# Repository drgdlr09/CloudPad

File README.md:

# CloudPad
A simple nine-key macropad that can open up my favorite and most-used apps

**Bill of Materials**
- Seeed XIAO RP2040
- 9 through-hole 1N4148 diodes
- 9 MX-style switches
- 9 white blank DSA keycaps
- 1 EC11 rotary encoder

I opted to use a simplified sandwich mount for ease of design and assembly. I may iterate on this in the future to make it more visually pleasing.

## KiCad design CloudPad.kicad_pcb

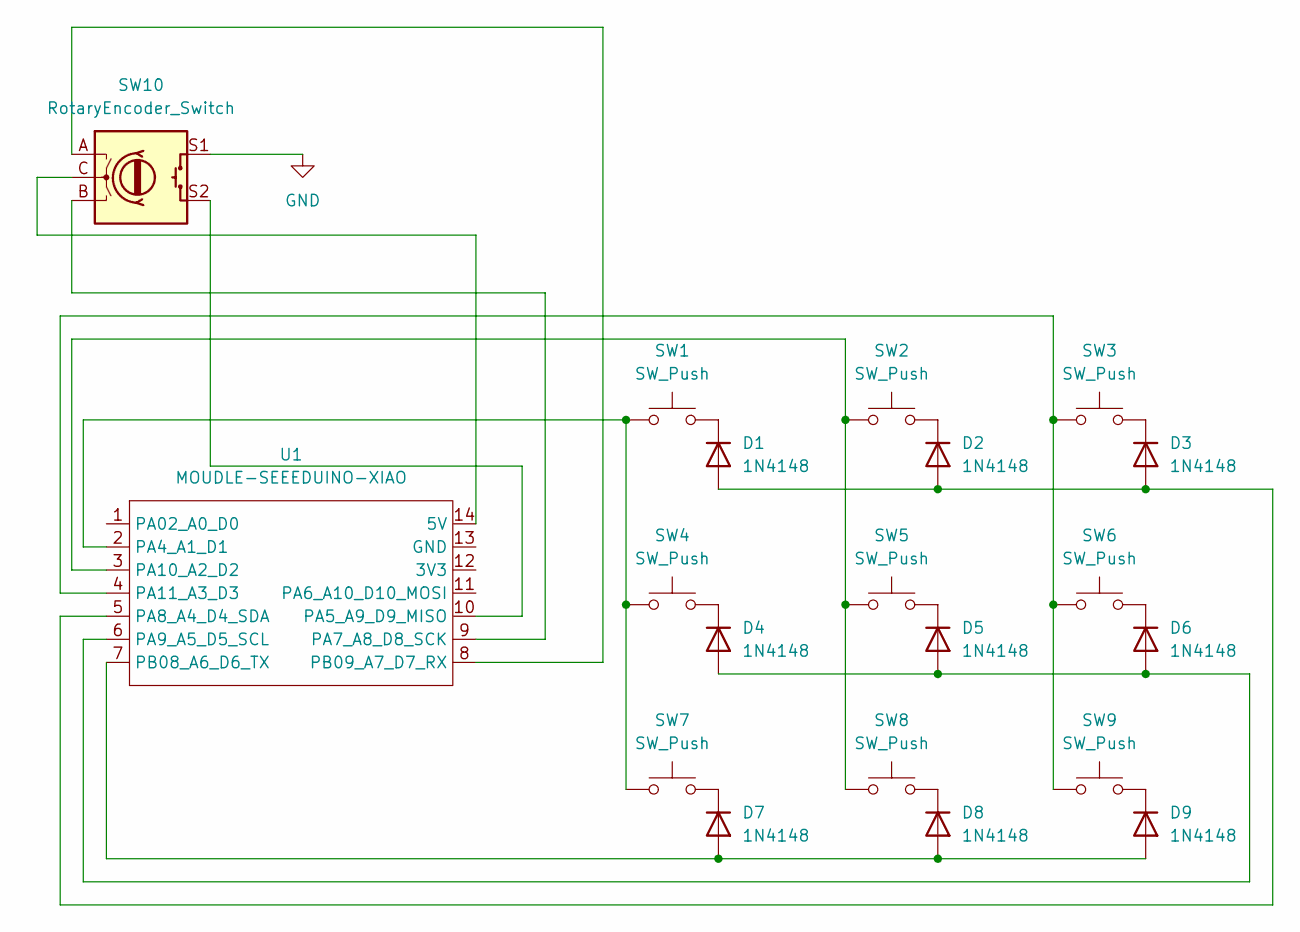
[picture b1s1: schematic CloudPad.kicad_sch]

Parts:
D1, D2, D3, D4, D5, D6, D7, D8, D9: 1N4148; D_DO-35_SOD27_P7.62mm_Horizontal
SW1, SW2, SW3, SW4, SW5, SW6, SW7, SW8, SW9: SW_Push; SW_Cherry_MX_1.00u_PCB
SW10: RotaryEncoder_Switch; RotaryEncoder_Alps_EC11E-Switch_Vertical_H20mm
U1: MOUDLE-SEEEDUINO-XIAO; XIAO-Generic-Hybrid-14P-2.54-21X17.8MM

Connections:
GND: SW10.S1
unnamed: D1.2 (A), D2.2 (A), D3.2 (A), U1.5 (PA8_A4_D4_SDA)
unnamed: D1.1 (K), SW1.2
unnamed: D2.1 (K), SW2.2
unnamed: D3.1 (K), SW3.2
unnamed: D4.2 (A), D5.2 (A), D6.2 (A), U1.6 (PA9_A5_D5_SCL)
unnamed: D4.1 (K), SW4.2
unnamed: D5.1 (K), SW5.2
unnamed: D6.1 (K), SW6.2
unnamed: D7.2 (A), D8.2 (A), D9.2 (A), U1.7 (PB08_A6_D6_TX)
unnamed: D7.1 (K), SW7.2
unnamed: D8.1 (K), SW8.2
unnamed: D9.1 (K), SW9.2
unnamed: SW10.C, U1.14 (5V)
unnamed: SW1.1, SW4.1, SW7.1, U1.2 (PA4_A1_D1)
unnamed: SW10.S2, U1.10 (PA5_A9_D9_MISO)
unnamed: SW10.B, U1.9 (PA7_A8_D8_SCK)
unnamed: SW2.1, SW5.1, SW8.1, U1.3 (PA10_A2_D2)
unnamed: SW3.1, SW6.1, SW9.1, U1.4 (PA11_A3_D3)
unnamed: SW10.A, U1.8 (PB09_A7_D7_RX)

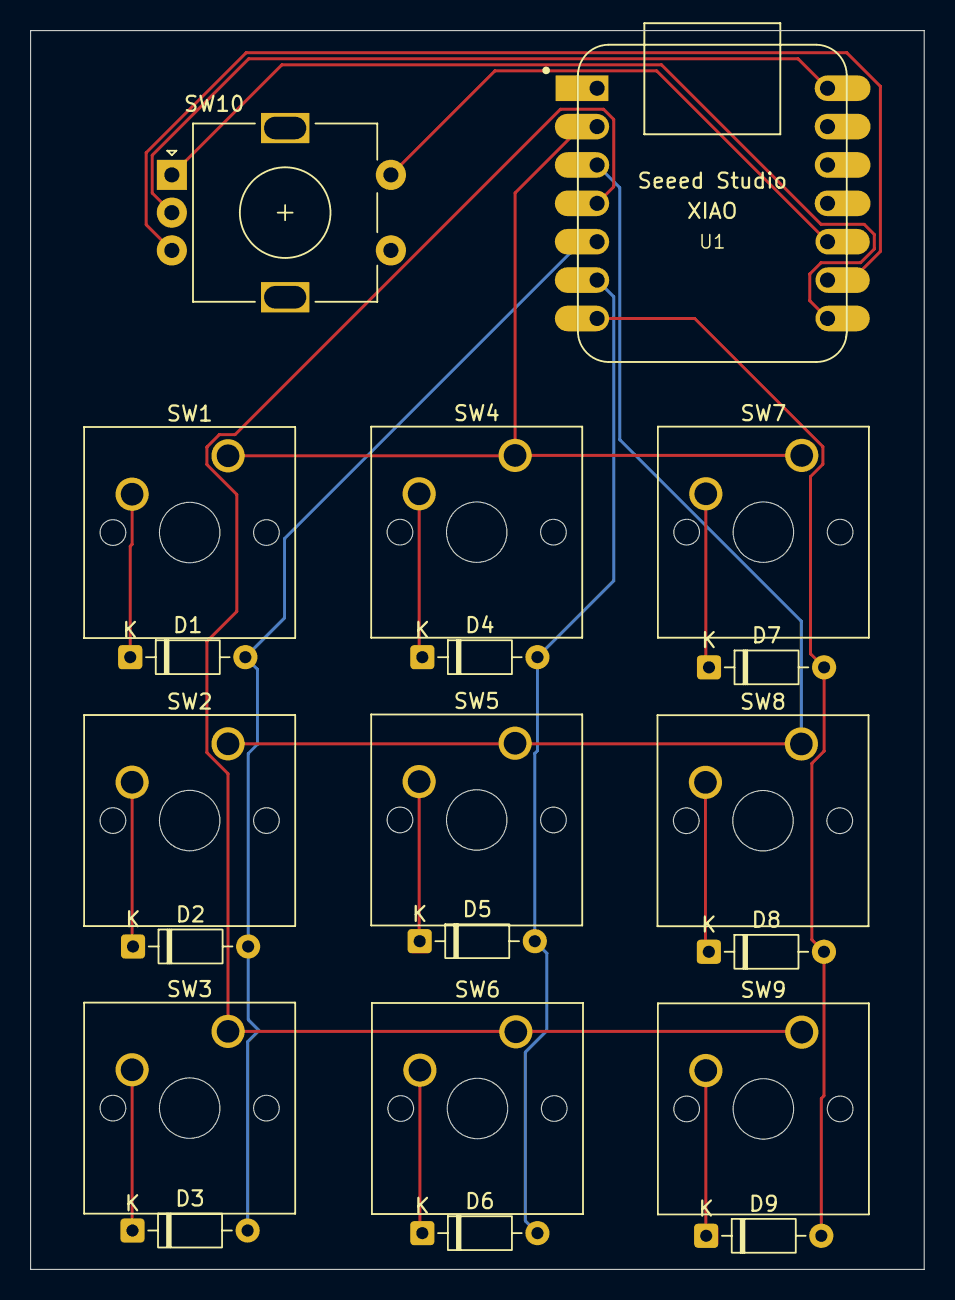
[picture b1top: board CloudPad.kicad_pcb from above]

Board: 2 copper layers, 59.2 x 82.0 mm, 20 parts (0 on the bottom side), 19 nets.
